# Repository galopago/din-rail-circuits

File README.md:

# DIN RAIL CIRCUITS

Collection of DIN RAIL mountable circuits!

Read this in other languages: [Español](docs/README.es.md)
## How to use this repository

The projects were developed in KiCad V5.1

## License

This is an Open Hardware project an is licensed under a [Creative Commons Attribution 4.0 International License](https://creativecommons.org/licenses/by/4.0/)

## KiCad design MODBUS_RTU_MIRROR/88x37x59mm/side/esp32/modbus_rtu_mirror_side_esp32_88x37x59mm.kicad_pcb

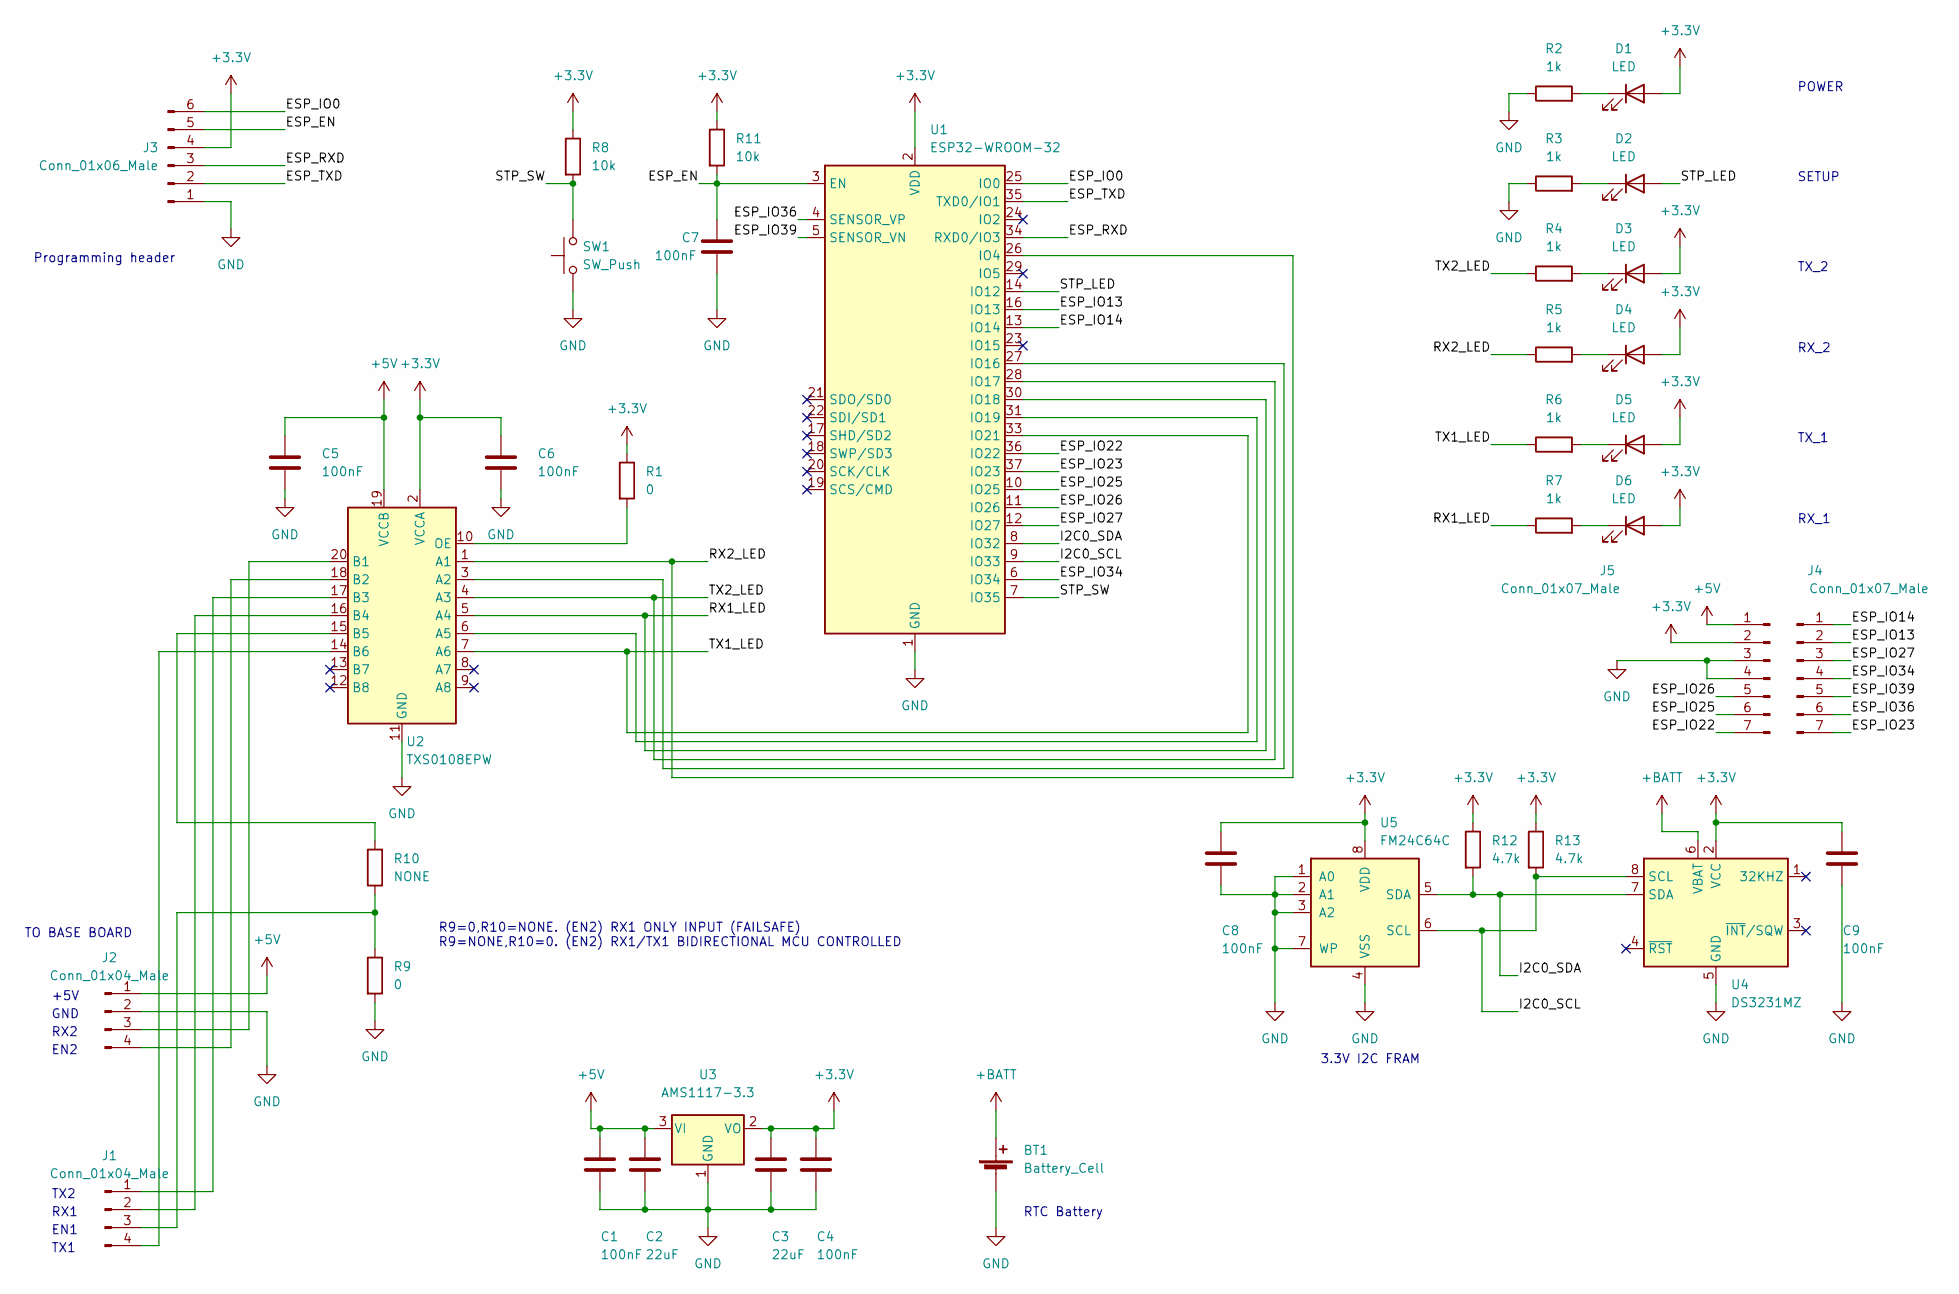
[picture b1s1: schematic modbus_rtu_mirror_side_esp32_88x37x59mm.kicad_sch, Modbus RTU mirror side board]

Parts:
BT1: Battery_Cell; CR2032_Vertical_CircularHoles
C1, C4, C5, C6, C7, C8, C9: 100nF; C_0805_2012Metric_Pad1.18x1.45mm_HandSolder
C2, C3: 22uF; C_0805_2012Metric_Pad1.18x1.45mm_HandSolder
D1, D2, D3, D4, D5, D6: LED; LED_D3.0mm_4.5x9.5mm
J1, J2: Conn_01x04_Male; PinHeader_1x04_P2.54mm_Vertical
J3: Conn_01x06_Male; PinHeader_1x06_P2.54mm_Vertical
J4, J5: Conn_01x07_Male; PinHeader_1x07_P1.00mm_Vertical
R1, R9: 0; R_0805_2012Metric_Pad1.20x1.40mm_HandSolder
R2, R3, R4, R5, R6, R7: 1k; R_0805_2012Metric_Pad1.20x1.40mm_HandSolder
R8, R11: 10k; R_0805_2012Metric_Pad1.20x1.40mm_HandSolder
R10: NONE; R_0805_2012Metric_Pad1.20x1.40mm_HandSolder
R12, R13: 4.7k; R_0805_2012Metric_Pad1.20x1.40mm_HandSolder
SW1: SW_Push; SW_Tactile_SPST_Angled_PTS645Vx31-2LFS
U1: ESP32-WROOM-32
U2: TXS0108EPW; TSSOP-20_4.4x6.5mm_P0.65mm
U3: AMS1117-3.3; SOT-223-3_TabPin2
U4: DS3231MZ; SOIC-8_3.9x4.9mm_P1.27mm
U5: FM24C64C; SOIC-8_3.9x4.9mm_P1.27mm

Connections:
+3.3V: C3.1, C4.1, C6.1, C8.1, C9.1, D1.2 (A), D3.2 (A), D4.2 (A), D5.2 (A), D6.2 (A), J3.4, R1.1, R8.1, R11.1, R12.1, R13.1, U1.2 (VDD), U2.2 (VCCA), U3.2 (VO), U4.2 (VCC), U5.8 (VDD)
+5V: C1.1, C2.1, C5.1, J2.1, U2.19 (VCCB), U3.3 (VI)
+BATT: BT1.1 (+), U4.6 (VBAT)
/ESP_EN: C7.1, J3.5, R11.2, U1.3 (EN)
/ESP_IO0: J3.6, U1.25 (IO0)
/ESP_IO13: J4.2, U1.16 (IO13)
/ESP_IO14: J4.1, U1.13 (IO14)
/ESP_IO22: J5.7, U1.36 (IO22)
/ESP_IO23: J4.7, U1.37 (IO23)
/ESP_IO25: J5.6, U1.10 (IO25)
/ESP_IO26: J5.5, U1.11 (IO26)
/ESP_IO27: J4.3, U1.12 (IO27)
/ESP_IO34: J4.4, U1.6 (IO34)
/ESP_IO36: J4.6, U1.4 (SENSOR_VP)
/ESP_IO39: J4.5, U1.5 (SENSOR_VN)
/ESP_RXD: J3.3, U1.34 (RXD0/IO3)
/ESP_TXD: J3.2, U1.35 (TXD0/IO1)
/I2C0_SCL: R13.2, U1.9 (IO33), U4.8 (SCL), U5.6 (SCL)
/I2C0_SDA: R12.2, U1.8 (IO32), U4.7 (SDA), U5.5 (SDA)
/RX1_LED: R7.1, U1.30 (IO18), U2.5 (A4)
/RX2_LED: R5.1, U1.26 (IO4), U2.1 (A1)
/STP_LED: D2.2 (A), U1.14 (IO12)
/STP_SW: R8.2, SW1.1, U1.7 (IO35)
/TX1_LED: R6.1, U1.33 (IO21), U2.7 (A6)
/TX2_LED: R4.1, U1.28 (IO17), U2.4 (A3)
GND: BT1.2 (-), C1.2, C2.2, C3.2, C4.2, C5.2, C6.2, C7.2, C8.2, C9.2, J2.2, J3.1, R2.1, R3.1, R9.2, SW1.2, U1.1 (GND), U1.15 (GND), U1.38 (GND), U1.39 (GND), U2.11 (GND), U3.1 (GND), U4.5 (GND), U5.1 (A0), U5.2 (A1), U5.3 (A2), U5.4 (VSS), U5.7 (WP)
unnamed: D1.1 (K), R2.2
unnamed: D2.1 (K), R3.2
unnamed: D3.1 (K), R4.2
unnamed: D4.1 (K), R5.2
unnamed: D5.1 (K), R6.2
unnamed: D6.1 (K), R7.2
unnamed: J1.1, U2.17 (B3)
unnamed: J1.2, U2.16 (B4)
unnamed: J1.3, R9.1, R10.1
unnamed: J1.4, U2.14 (B6)
unnamed: J2.3, U2.20 (B1)
unnamed: J2.4, U2.18 (B2)
unnamed: R1.2, U2.10 (OE)
unnamed: R10.2, U2.15 (B5)
unnamed: U1.27 (IO16), U2.3 (A2)
unnamed: U1.31 (IO19), U2.6 (A5)

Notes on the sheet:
TO BASE BOARD
RX1
TX_2
EN2
RX2
RTC Battery
EN1
R9=0,R10=NONE. (EN2) RX1 ONLY INPUT (FAILSAFE) R9=NONE,R10=0. (EN2) RX1/TX1 BIDIRECTIONAL MCU CONTROLLED
TX2
GND
SETUP
Programming header
+5V
3.3V I2C FRAM
RX_1
TX_1
TX1
POWER
RX_2

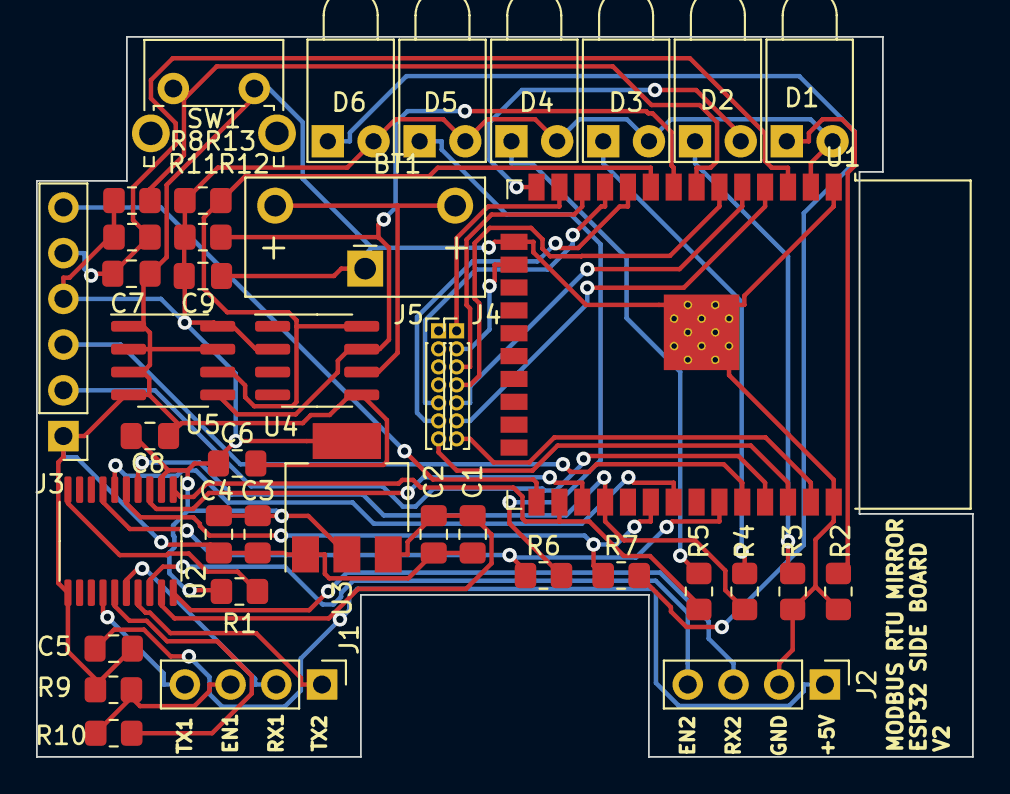
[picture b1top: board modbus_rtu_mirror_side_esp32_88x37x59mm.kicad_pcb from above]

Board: 2 copper layers, 52.0 x 40.0 mm, 40 parts (0 on the bottom side), 42 nets.

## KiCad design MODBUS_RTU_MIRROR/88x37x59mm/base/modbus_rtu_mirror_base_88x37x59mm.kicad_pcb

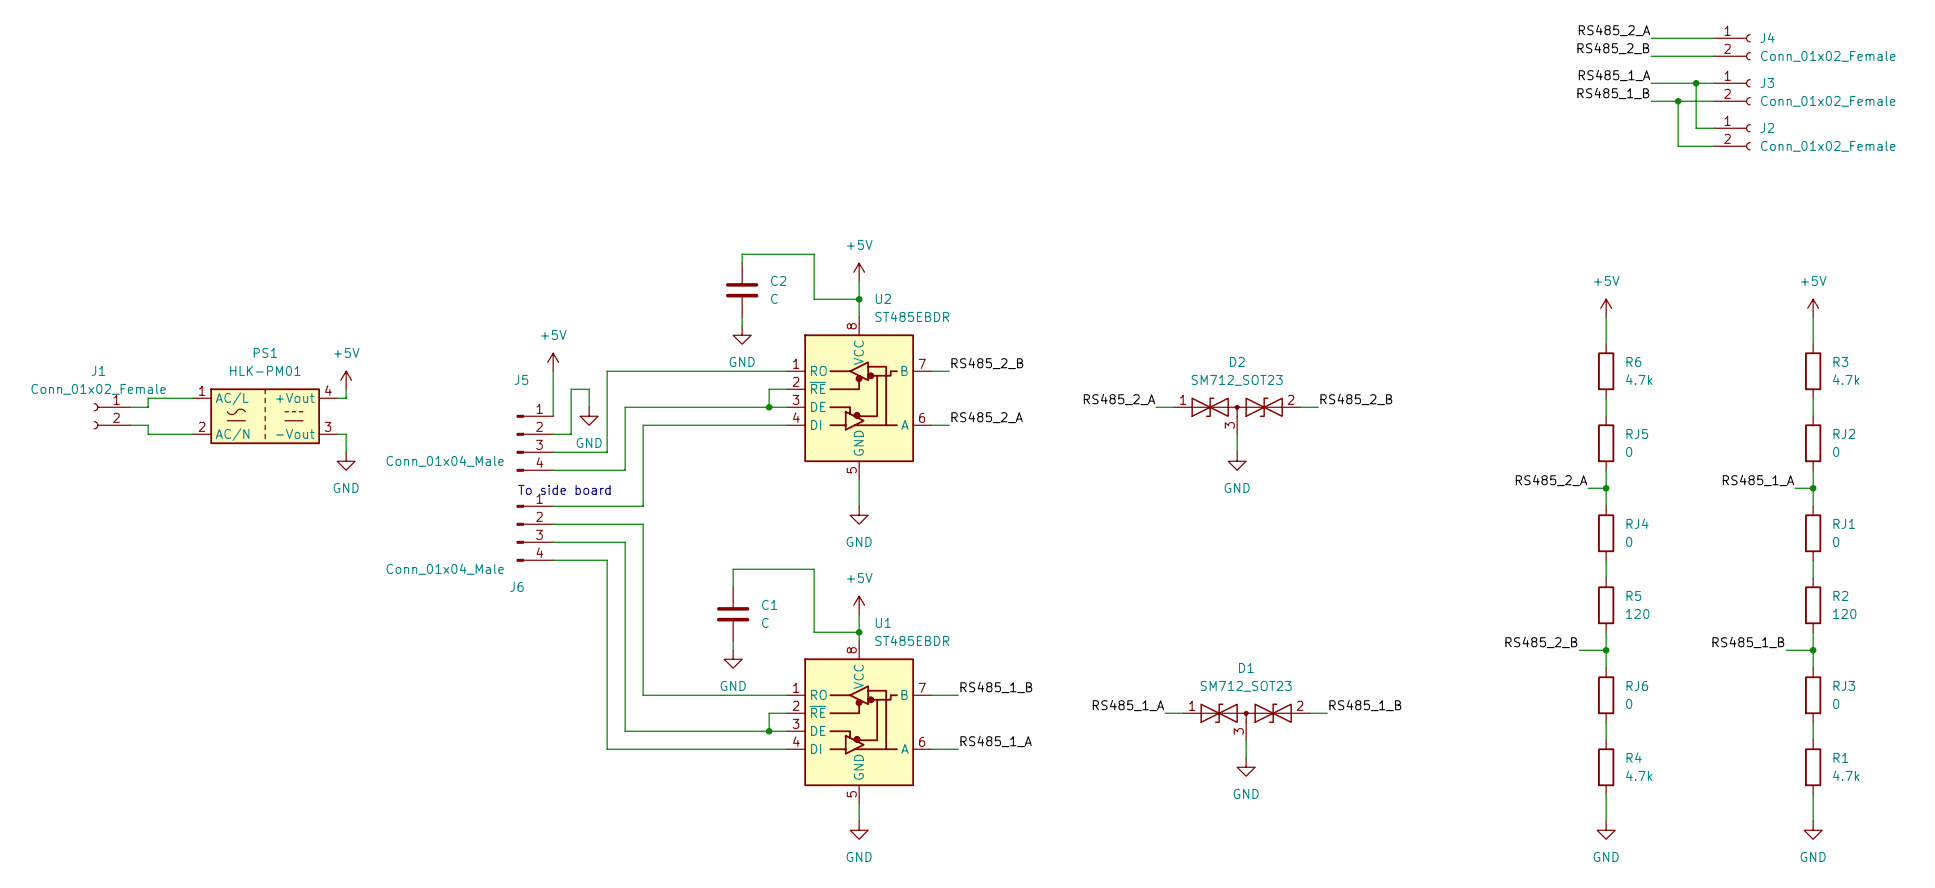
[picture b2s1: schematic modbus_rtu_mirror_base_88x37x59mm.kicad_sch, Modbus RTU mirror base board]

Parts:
C1, C2: C; C_0805_2012Metric_Pad1.18x1.45mm_HandSolder
D1, D2: SM712_SOT23; SOT-23
J1, J2, J3, J4: Conn_01x02_Female; TerminalBlock_RND_205-00012_1x02_P5.00mm_Horizontal
J5, J6: Conn_01x04_Male; PinHeader_1x04_P2.54mm_Vertical
PS1: HLK-PM01; Converter_ACDC_HiLink_HLK-PMxx
R1, R3, R4, R6: 4.7k; R_0805_2012Metric_Pad1.20x1.40mm_HandSolder
R2, R5: 120; R_0805_2012Metric_Pad1.20x1.40mm_HandSolder
RJ1, RJ2, RJ3, RJ4, RJ5, RJ6: 0; R_0805_2012Metric_Pad1.20x1.40mm_HandSolder
U1, U2: ST485EBDR; SOIC-8_3.9x4.9mm_P1.27mm

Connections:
+5V: C1.1, C2.1, J5.1, PS1.4 (+Vout), R3.1, R6.1, U1.8 (VCC), U2.8 (VCC)
/RS485_1_A: D1.1 (A1), J2.1, J3.1, RJ1.1, RJ2.2, U1.6 (A)
/RS485_1_B: D1.2 (A2), J2.2, J3.2, R2.2, RJ3.1, U1.7 (B)
/RS485_2_A: D2.1 (A1), J4.1, RJ4.1, RJ5.2, U2.6 (A)
/RS485_2_B: D2.2 (A2), J4.2, R5.2, RJ6.1, U2.7 (B)
GND: C1.2, C2.2, D1.3 (common), D2.3 (common), J5.2, PS1.3 (-Vout), R1.2, R4.2, U1.5 (GND), U2.5 (GND)
unnamed: J6.2, U1.1 (RO)
unnamed: J6.3, U1.2 (~RE), U1.3 (DE)
unnamed: J6.4, U1.4 (DI)
unnamed: J1.1, PS1.1 (AC/L)
unnamed: J1.2, PS1.2 (AC/N)
unnamed: R1.1, RJ3.2
unnamed: R3.2, RJ2.1
unnamed: R4.1, RJ6.2
unnamed: R5.1, RJ4.2
unnamed: R6.2, RJ5.1
unnamed: R2.1, RJ1.2
unnamed: J5.3, U2.1 (RO)
unnamed: J5.4, U2.2 (~RE), U2.3 (DE)
unnamed: J6.1, U2.4 (DI)

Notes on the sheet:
To side board

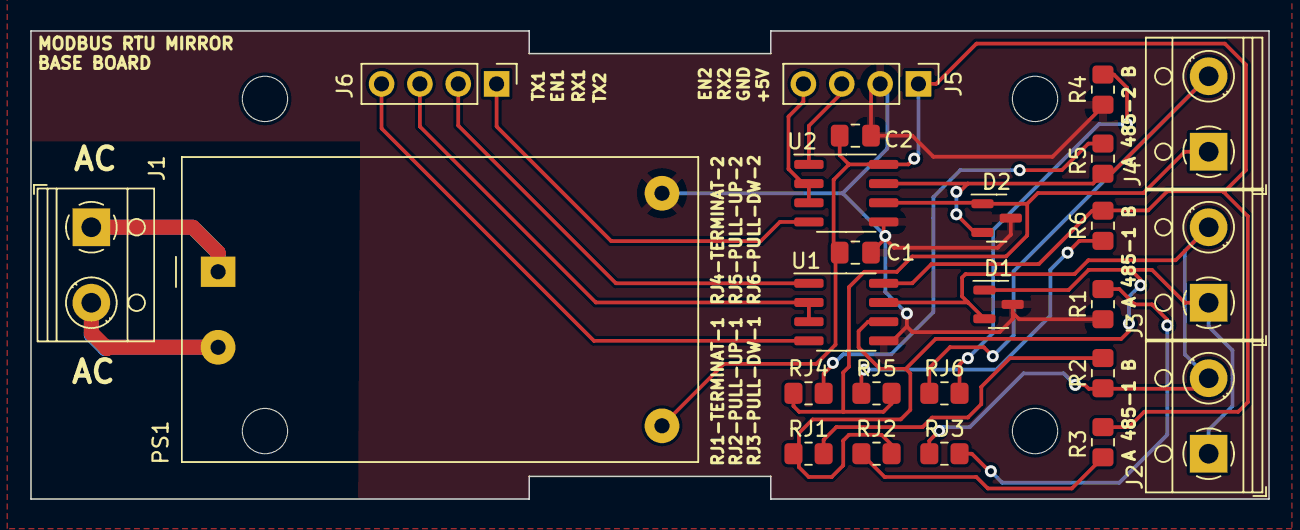
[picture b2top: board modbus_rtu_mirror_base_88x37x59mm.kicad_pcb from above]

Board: 2 copper layers, 82.0 x 31.0 mm, 29 parts (0 on the bottom side), 20 nets.

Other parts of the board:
MH00, MH01, MH02, MH03: MountingHole_3mm

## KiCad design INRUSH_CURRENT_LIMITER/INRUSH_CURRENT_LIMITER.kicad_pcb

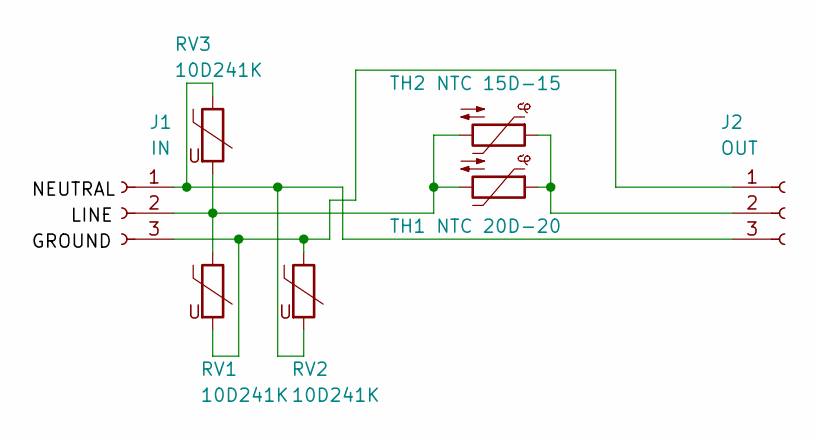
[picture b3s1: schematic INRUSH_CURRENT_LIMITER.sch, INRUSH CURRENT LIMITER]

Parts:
J1: IN; TerminalBlock_Phoenix_MKDS-1,5-3-5.08_1x03_P5.08mm_Horizont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
J2: OUT; TerminalBlock_Phoenix_MKDS-1,5-3-5.08_1x03_P5.08mm_Horizont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
RV1, RV2, RV3: 10D241K; RV_Disc_D12mm_W3.9mm_P7.5mm
TH1: NTC 20D-20; RV_Disc_D21.5mm_W5.3mm_P10mm
TH2: NTC 15D-15; RV_Disc_D15.5mm_W6.1mm_P7.5mm

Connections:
unnamed: J1.1, J2.3, RV2.2, RV3.1
unnamed: J1.2, RV1.1, RV3.2, TH1.2, TH2.2
unnamed: J1.3, J2.1, RV1.2, RV2.1
unnamed: J2.2, TH1.1, TH2.1

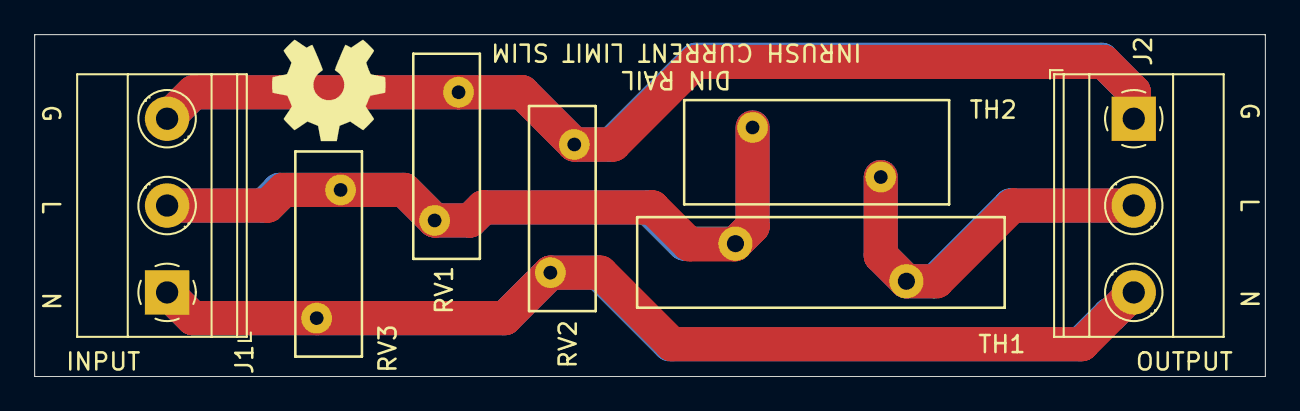
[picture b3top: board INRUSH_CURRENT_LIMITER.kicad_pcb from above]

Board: 2 copper layers, 72.0 x 20.0 mm, 7 parts (0 on the bottom side), 4 nets.

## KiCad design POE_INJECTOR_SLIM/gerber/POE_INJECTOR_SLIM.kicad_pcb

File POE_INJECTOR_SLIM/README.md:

# DIN RAIL PASSIVE POE INJECTOR SLIM

Passive PoE injector, din rail mountable. slim 20 x 72 mm aprox. Up to 48V, led indicator, 1.1 A 72V polyfuse protection.

Read this in other languages: [Español](docs/README.es.md)
## How to use this repository

The project is developed in KiCad V5.1

## Directory structure

* The root folder contains KiCad files: project, schematic and PCB
* gerber/single directory contains ready to manufacture files, for a single board.
* gerber/panel_100mmx100mm directory contains ready to manufacture files that fits in a 100mm x 100mm panel (use Vcuts!).
* docs additional files

## License

This is an Open Hardware project an is licensed under a [Creative Commons Attribution 4.0 International License](https://creativecommons.org/licenses/by/4.0/)

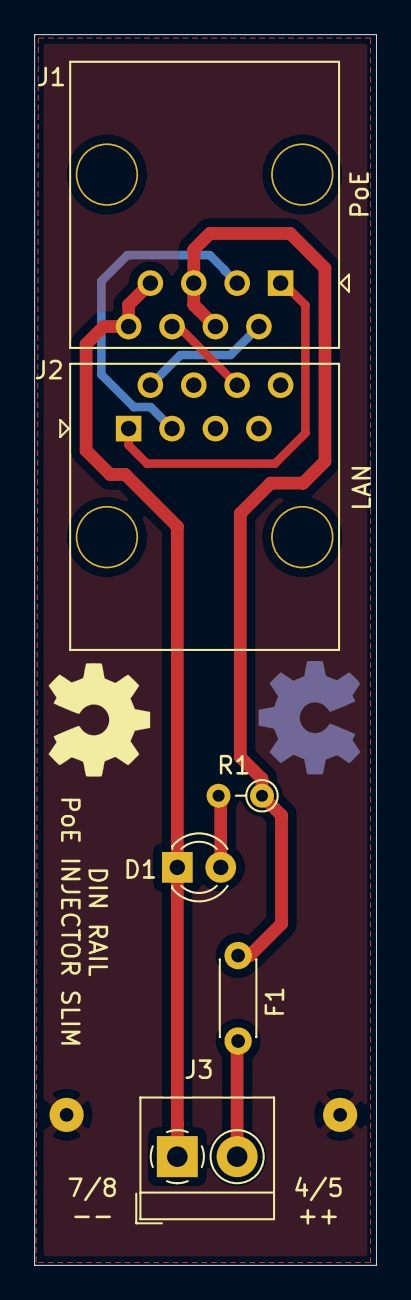
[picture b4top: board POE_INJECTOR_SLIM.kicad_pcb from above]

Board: 2 copper layers, 20.0 x 72.0 mm, 8 parts (0 on the bottom side), 9 nets.

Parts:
D1: LED_Small; LED_D3.0mm
F1: Polyfuse_Small; C_Disc_D4.3mm_W1.9mm_P5.00mm
J1, J2: RJ45; RJ45_OST_PJ012-8P8CX_Vertical
J3: Conn_01x02_Female; TerminalBlock_4Ucon_1x02_P3.50mm_Horizontal
J4, J5: Conn_01x01_Male; SolderWirePad_1x01_Drill0.8mm
R1: R; R_Axial_DIN0204_L3.6mm_D1.6mm_P2.54mm_Vertical

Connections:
unnamed: D1.1, J1.7, J1.8, J3.1
unnamed: D1.2, R1.2
unnamed: F1.1, J3.2
unnamed: F1.2, J1.4, J1.5, R1.1
unnamed: J1.1, J2.1
unnamed: J1.2, J2.2
unnamed: J1.3, J2.3
unnamed: J1.6, J2.6
unnamed: J4.1, J5.1

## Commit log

2021-08-12 moved other projects to this repo
2021-08-12 all traces routed
2021-08-13 single gerber
2021-09-07 silkscreen labels
2021-09-07 renamed project
2021-09-08 silks adjusted
2021-09-08 single gerbers
2021-09-08 soldermask fixed
2021-09-08 panel gerbers
2021-09-09 first draft
2021-09-09 minor adjustments to holes
2021-09-09 copper plates and silks
2021-09-15 readme first improvements
2021-09-15 readme improvements
2021-09-15 readme eng improvements
2021-09-15 readme es
2021-09-15 readme es+
2021-09-15 readme es++
2021-09-15 LICENSE
2021-09-15 license link
2021-09-15 license link fix
2021-09-15 license link image test
2021-09-15 license link image test space
2021-09-15 license link image cc
2021-09-15 license link image cc fix
2021-09-15 main image
2021-09-15 main image fix
2021-09-15 main image fix+
2021-09-15 readme esp img
2021-09-15 readme esp ok
2021-09-16 poe slim readme
2021-09-16 poe slim readme +
2021-09-16 poe slim readme ++
2021-09-16 poe slim readme +++
2021-09-16 poe slim readme ++++
2021-09-16 poe slim readme ES
2021-09-16 poe slim readme ES+
2021-09-16 poe slim readme ES++
2021-09-16 poe slim readme ES+++
2021-09-16 fixed img extension
2021-09-16 poe injector readme
2021-09-16 poe injector tech draw
2021-09-16 poe injector ES readme
2021-09-16 oem hub initial docs
2021-09-16 slim eth hub readme
2021-09-16 slim eth hub readme+
2021-09-16 enlgish version fixed link
2021-09-16 slim eth hub ES readme
2021-09-16 inrush limiter
2021-09-16 inrush limiter ES readme
2021-09-16 inrush limiter ES image link fix
2021-09-16 inrush limiter ES typo
2021-09-16 inrush limiter ES EN link
2021-09-16 inrush limiter ES EN link fix
2021-09-16 EN links from ES fix
2021-09-16 poe injctor slim en link
2021-09-16 poe injctor slim en link+
2021-09-16 en links+
2021-09-16 misc img fixes
2021-09-16 misc img fixes+
2021-10-08 resistor and polyswitch values
2024-08-27 started blank modbus rtu project
2024-08-28 started base 88x37x59
2024-08-30 enlarged holes, started putting some components
2024-09-19 added RS485 terminals
2024-09-20 addes 2x rs485 chip
2024-09-27 started side board
2024-09-29 added capacitors, rtc, prog header
2024-09-30 added leds and pushbutton
2024-10-03 added vertical CR2032 connector
2024-10-06 all elements placed
2024-10-06 silk minor updates
2024-11-09 created folder for different processor version
2024-11-09 updated pcb silk
2024-12-03 created 90 degree 3mm led socket holder
2024-12-07 changed leds to horizontal and fixed TX1/RX1 disable/enable resistor
2025-02-02 minor modiffications
2025-02-07 started new branch test, with expansion header
2025-02-08 expansion connector routed
